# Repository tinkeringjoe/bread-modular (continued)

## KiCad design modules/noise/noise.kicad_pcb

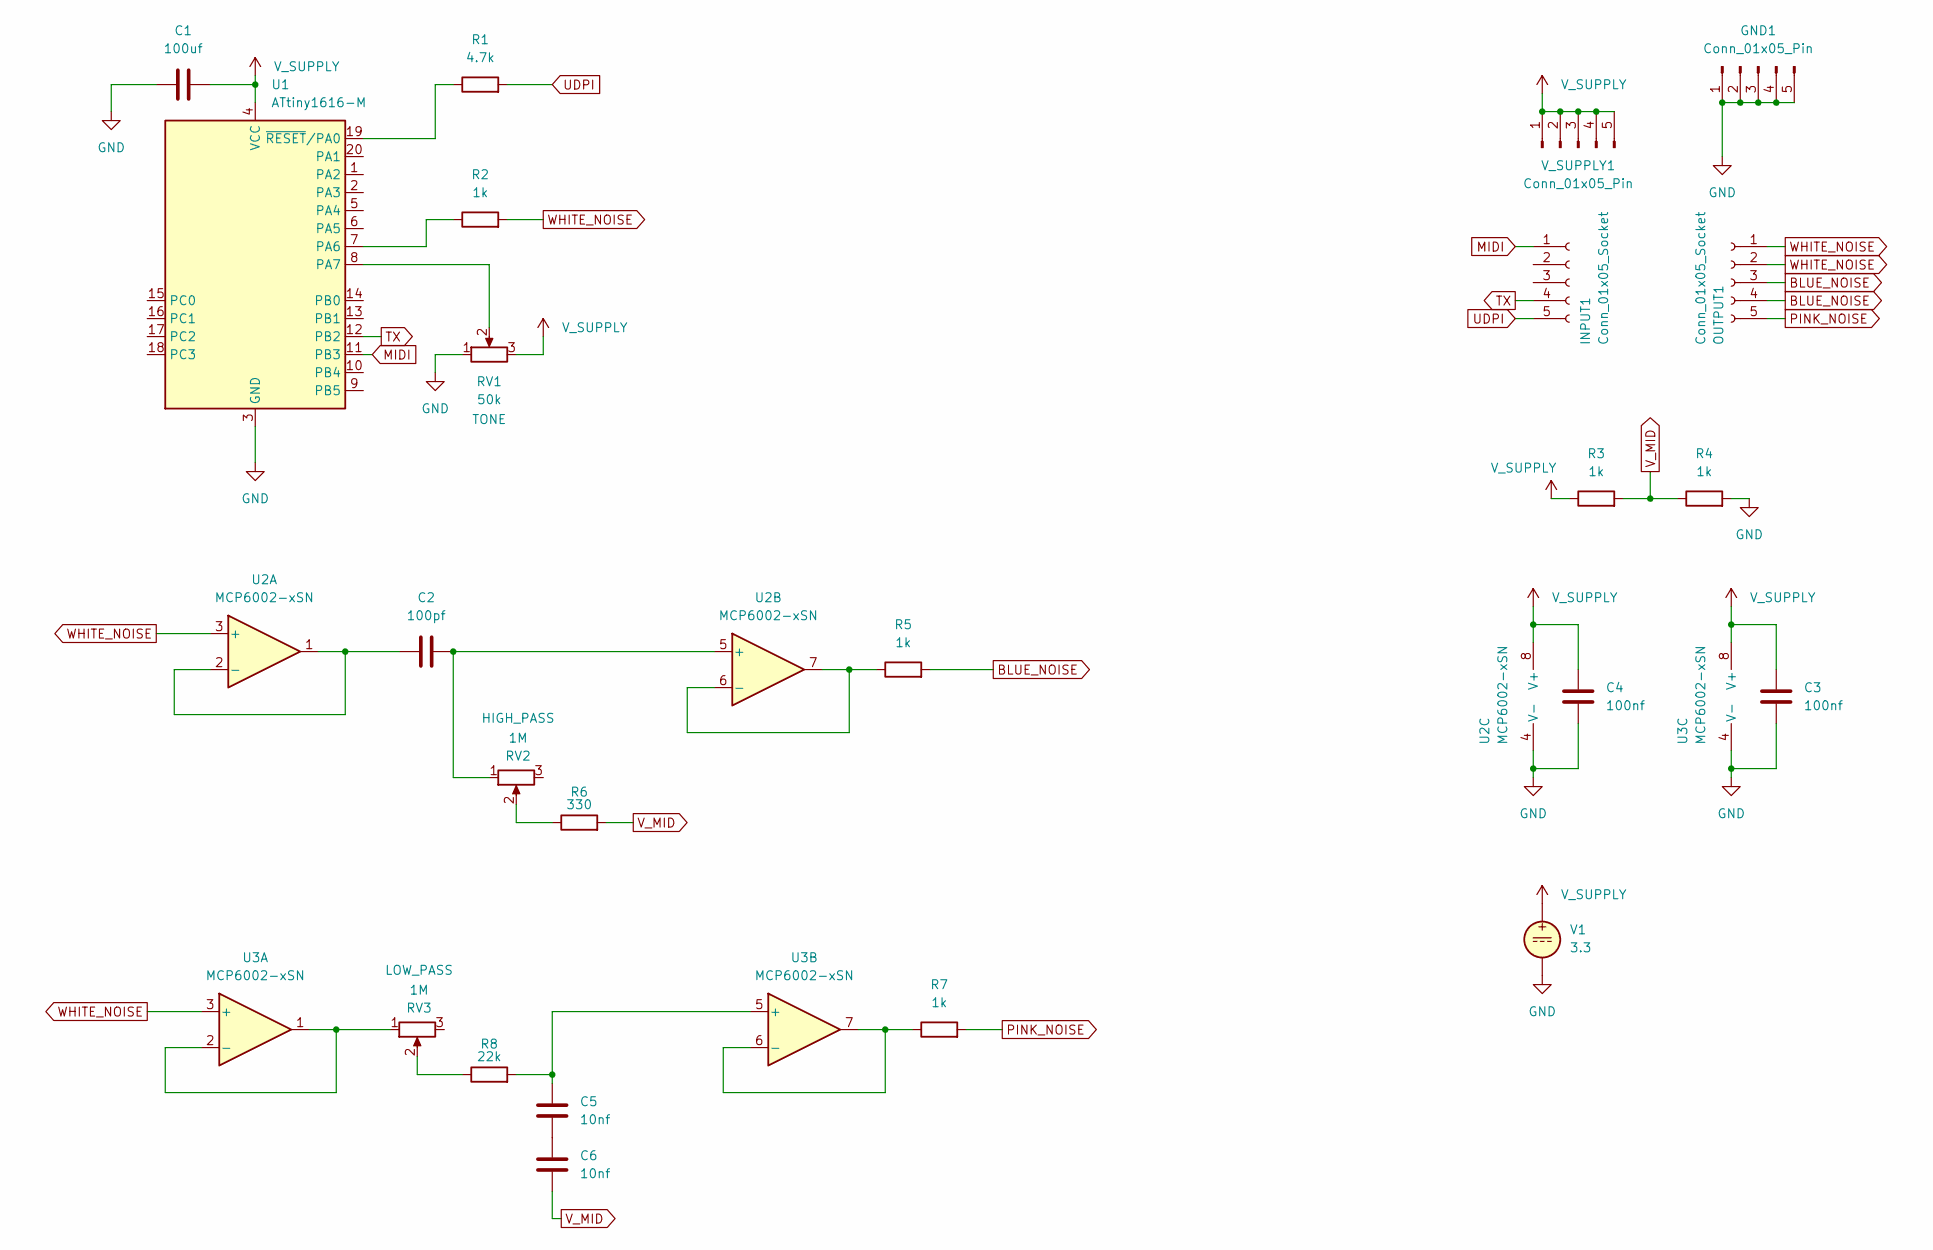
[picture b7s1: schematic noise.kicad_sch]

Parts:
C1: 100uf; C_1206_3216Metric
C2: 100pf; C_0402_1005Metric
C3, C4: 100nf; C_0402_1005Metric
C5, C6: 10nf; C_0402_1005Metric
GND1: Conn_01x05_Pin; Power_Connector
INPUT1: Conn_01x05_Socket; PinSocket_1x05_P2.54mm_Vertical
OUTPUT1: Conn_01x05_Socket; PinSocket_1x05_P2.54mm_Vertical
R1: 4.7k; R_0402_1005Metric
R2, R3, R4, R5, R7: 1k; R_0402_1005Metric
R6: 330; R_0402_1005Metric
R8: 22k; R_0402_1005Metric
RV1: 50k; Potentiometer_RV09
RV2, RV3: 1M; Potentiometer_RV09
U1: ATtiny1616-M; VQFN-20-1EP_3x3mm_P0.4mm_EP1.7x1.7mm
U2, U3: MCP6002-xSN; SOIC-8-1EP_3.9x4.9mm_P1.27mm_EP2.29x3mm
V1: 3.3
V_SUPPLY1: Conn_01x05_Pin; Power_Connector

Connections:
BLUE_NOISE: OUTPUT1.3, OUTPUT1.4, R5.2
GND: C1.1, C3.1, C4.1, GND1.1, GND1.2, GND1.3, GND1.4, GND1.5, R4.2, RV1.1, U1.3 (GND), U1.21 (GND), U2.4 (V-), U3.4 (V-), V1.2
MIDI: INPUT1.1, U1.11 (PB3)
unnamed: C5.1, C6.2
unnamed: R6.1, RV2.2
unnamed: R8.1, RV3.2
unnamed: R2.1, U1.7 (PA6)
unnamed: RV1.2, U1.8 (PA7)
unnamed: R1.1, U1.19 (~RESET/PA0)
unnamed: C2.1, U2.1, U2.2 (-)
unnamed: C2.2, RV2.1, U2.5 (+)
unnamed: R5.1, U2.6 (-), U2.7
unnamed: RV3.1, U3.1, U3.2 (-)
unnamed: C5.2, R8.2, U3.5 (+)
unnamed: R7.1, U3.6 (-), U3.7
PINK_NOISE: OUTPUT1.5, R7.2
TX: INPUT1.4, U1.12 (PB2)
UDPI: INPUT1.5, R1.2
V_MID: C6.1, R3.2, R4.1, R6.2
V_SUPPLY: C1.2, C3.2, C4.2, R3.1, RV1.3, U1.4 (VCC), U2.8 (V+), U3.8 (V+), V1.1, V_SUPPLY1.1, V_SUPPLY1.2, V_SUPPLY1.3, V_SUPPLY1.4, V_SUPPLY1.5
WHITE_NOISE: OUTPUT1.1, OUTPUT1.2, R2.2, U2.3 (+), U3.3 (+)

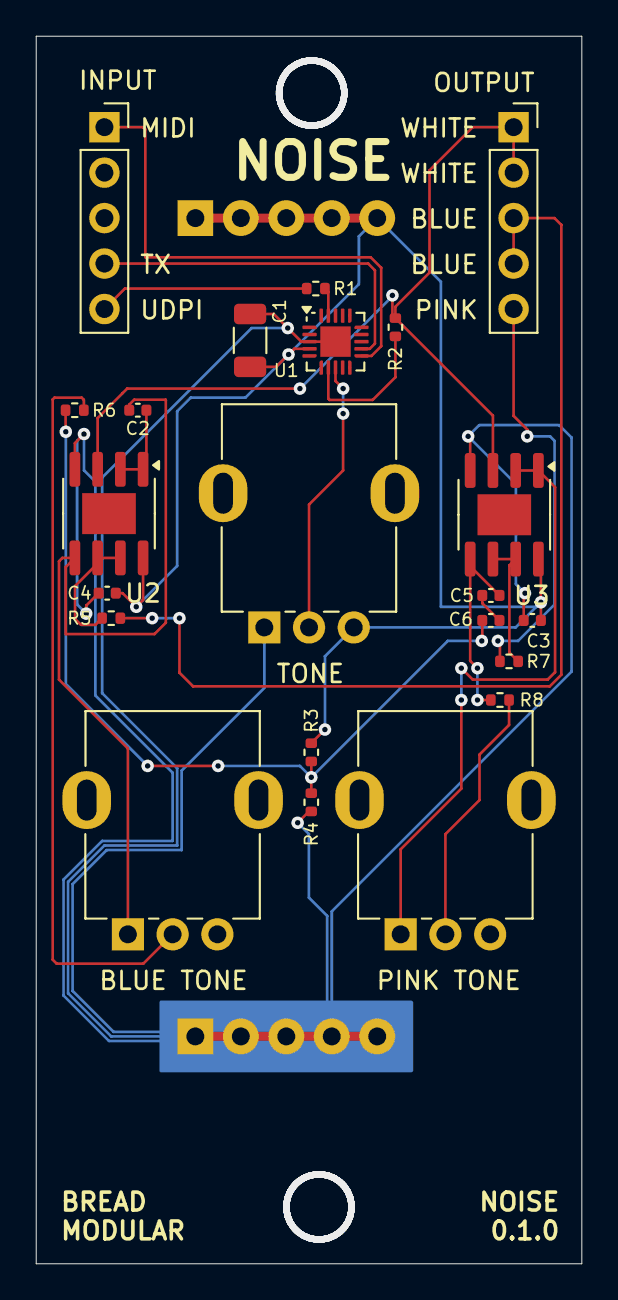
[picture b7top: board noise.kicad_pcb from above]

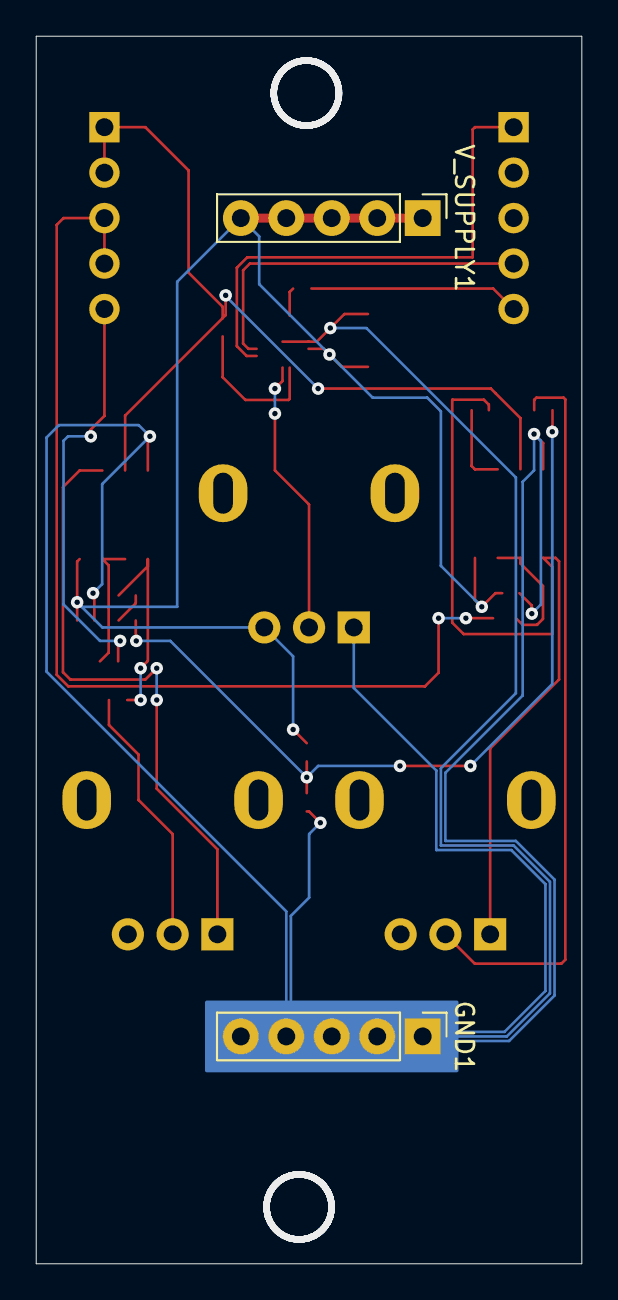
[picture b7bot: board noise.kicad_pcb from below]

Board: 2 copper layers, 30.5 x 68.6 mm, 24 parts (2 on the bottom side), 21 nets.

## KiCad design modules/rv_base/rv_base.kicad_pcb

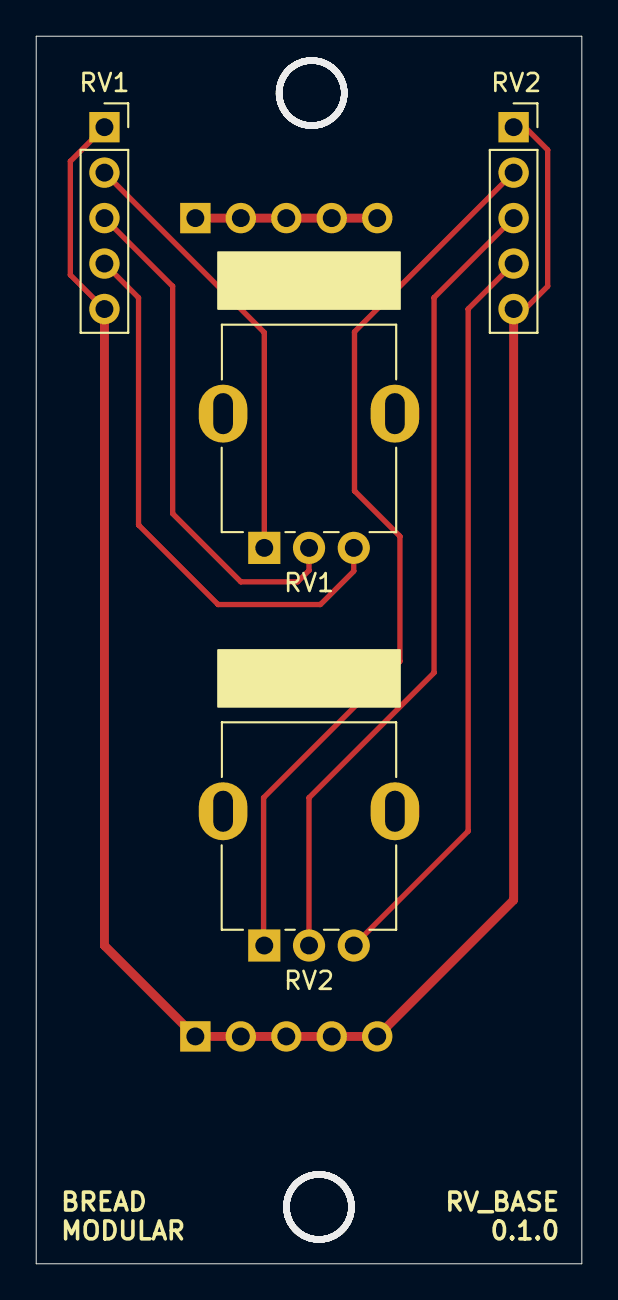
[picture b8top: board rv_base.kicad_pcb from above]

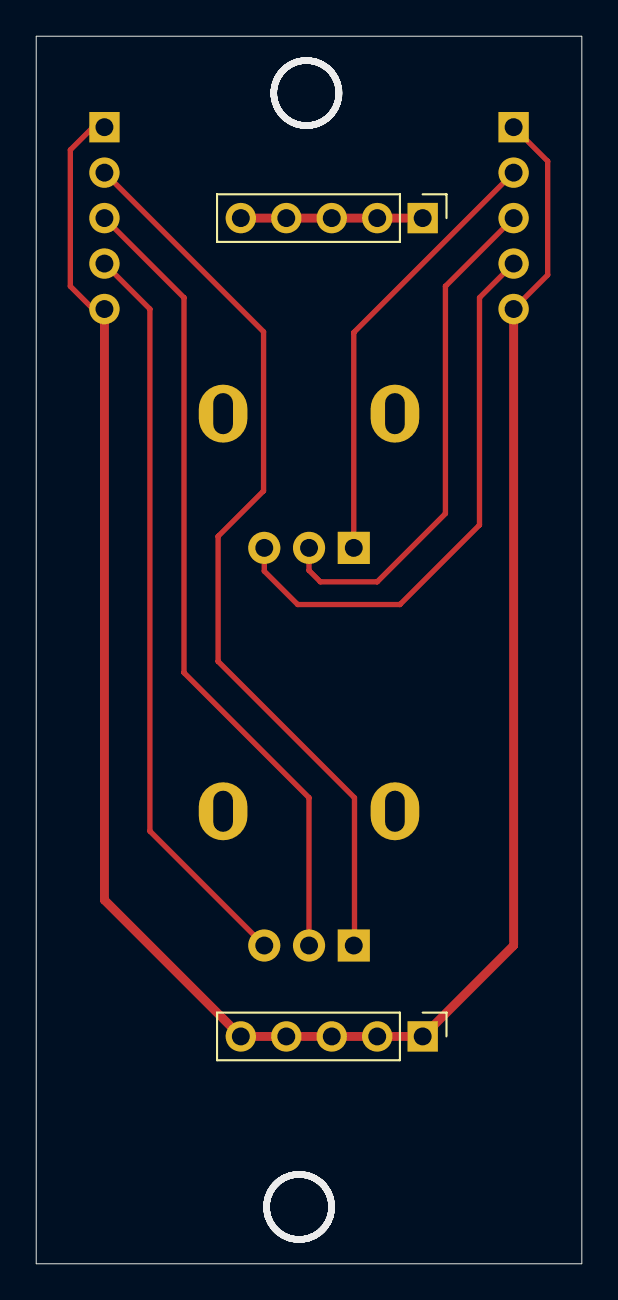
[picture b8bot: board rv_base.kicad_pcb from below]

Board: 2 copper layers, 30.5 x 68.6 mm, 6 parts (2 on the bottom side), 8 nets.

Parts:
5V1: Conn_01x05_Pin; PinHeader_1x05_P2.54mm_Vertical
GND1: Conn_01x05_Pin; PinHeader_1x05_P2.54mm_Vertical
INPUT1: Conn_01x05_Socket; PinSocket_1x05_P2.54mm_Vertical
OUTPUT2: Conn_01x05_Socket; PinSocket_1x05_P2.54mm_Vertical
RV1, RV2: R_Potentiometer; Potentiometer_RV09

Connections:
+5V: 5V1.1, 5V1.2, 5V1.3, 5V1.4, 5V1.5
GND: GND1.1, GND1.2, GND1.3, GND1.4, GND1.5, INPUT1.1, INPUT1.5, OUTPUT2.1, OUTPUT2.5
RV1_1: INPUT1.2, RV1.1
RV1_2: INPUT1.3, RV1.2
RV1_3: INPUT1.4, RV1.3
RV2_1: OUTPUT2.2, RV2.1
RV2_2: OUTPUT2.3, RV2.2
RV2_3: OUTPUT2.4, RV2.3
